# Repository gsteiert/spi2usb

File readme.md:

# SPI2USB

This is a USB adapter for the EK-10M08E144 MAX 10 Evaluation Kit.  
It adds a micro USB connector by connecting to the SPI connector J11.

## Connections

|  USB  |  J11  | 10M08E144             |
| :---: | :---: | :---                  |
|  D+   |   3   | 70, DIFFIO_TX_RX_B27P |
|  D-   |   1   | 69, DIFFIO_TX_RX_B27N |
|  PU   |   4   | 66, DIFFIO_TX_RX_B25N |
|  GND  |   6   |                       |
|  VBUS |   2   |                       |

## Schematic

[Schematic](spi2usb-sch.pdf)

## BOM 

 * [Micro USB Connector: 10118193-0001LF](https://www.mouser.com/ProductDetail/649-10118193-0001LF)
 * [2x 24 Ohm 0603 Thick Film Resistor: RC0603FR-0724RL](https://www.mouser.com/ProductDetail/603-RC0603FR-0724RL)
 * [1.5K Ohm 0603 Thick Film Resistor: RC0603FR-7W1K5L](https://www.mouser.com/ProductDetail/603-RC0603FR-7W1K5L)
 * [2x3 SMT Bottom Entry Socket: HLE-103-02-F-DV-BE-TR](https://www.mouser.com/ProductDetail/200-HLE10302FDVBETR) (optional)

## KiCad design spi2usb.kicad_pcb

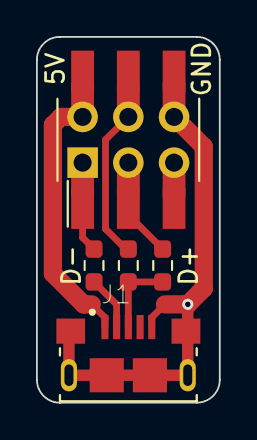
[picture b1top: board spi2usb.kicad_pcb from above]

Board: 2 copper layers, 10.2 x 20.3 mm, 6 parts (1 on the bottom side), 7 nets.

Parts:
D+: 33; R_0603_1608Metric_Pad0.98x0.95mm_HandSolder
D-: 33; R_0603_1608Metric_Pad0.98x0.95mm_HandSolder
GS1: GS_logo; gs_logo_200mil
J1: USB_B_Micro; FCI_10118193-0001LF-shield6
J2: Conn_02x03_Odd_Even; HDR_2x03_Dual
R3: 1.5K; R_0603_1608Metric_Pad0.98x0.95mm_HandSolder

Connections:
/D+: D+.1, J2.3
/D-: D-.1, J2.1
GND: GS1.1, J1.5, J1.6, J2.6
unnamed: J1.1, J2.2
unnamed: D-.2, J1.2
unnamed: D+.2, J1.3, R3.2
unnamed: J2.4, R3.1

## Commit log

2022-12-19 adding images and sch plot
2022-12-21 more details in readme
2022-12-24 added pin table
